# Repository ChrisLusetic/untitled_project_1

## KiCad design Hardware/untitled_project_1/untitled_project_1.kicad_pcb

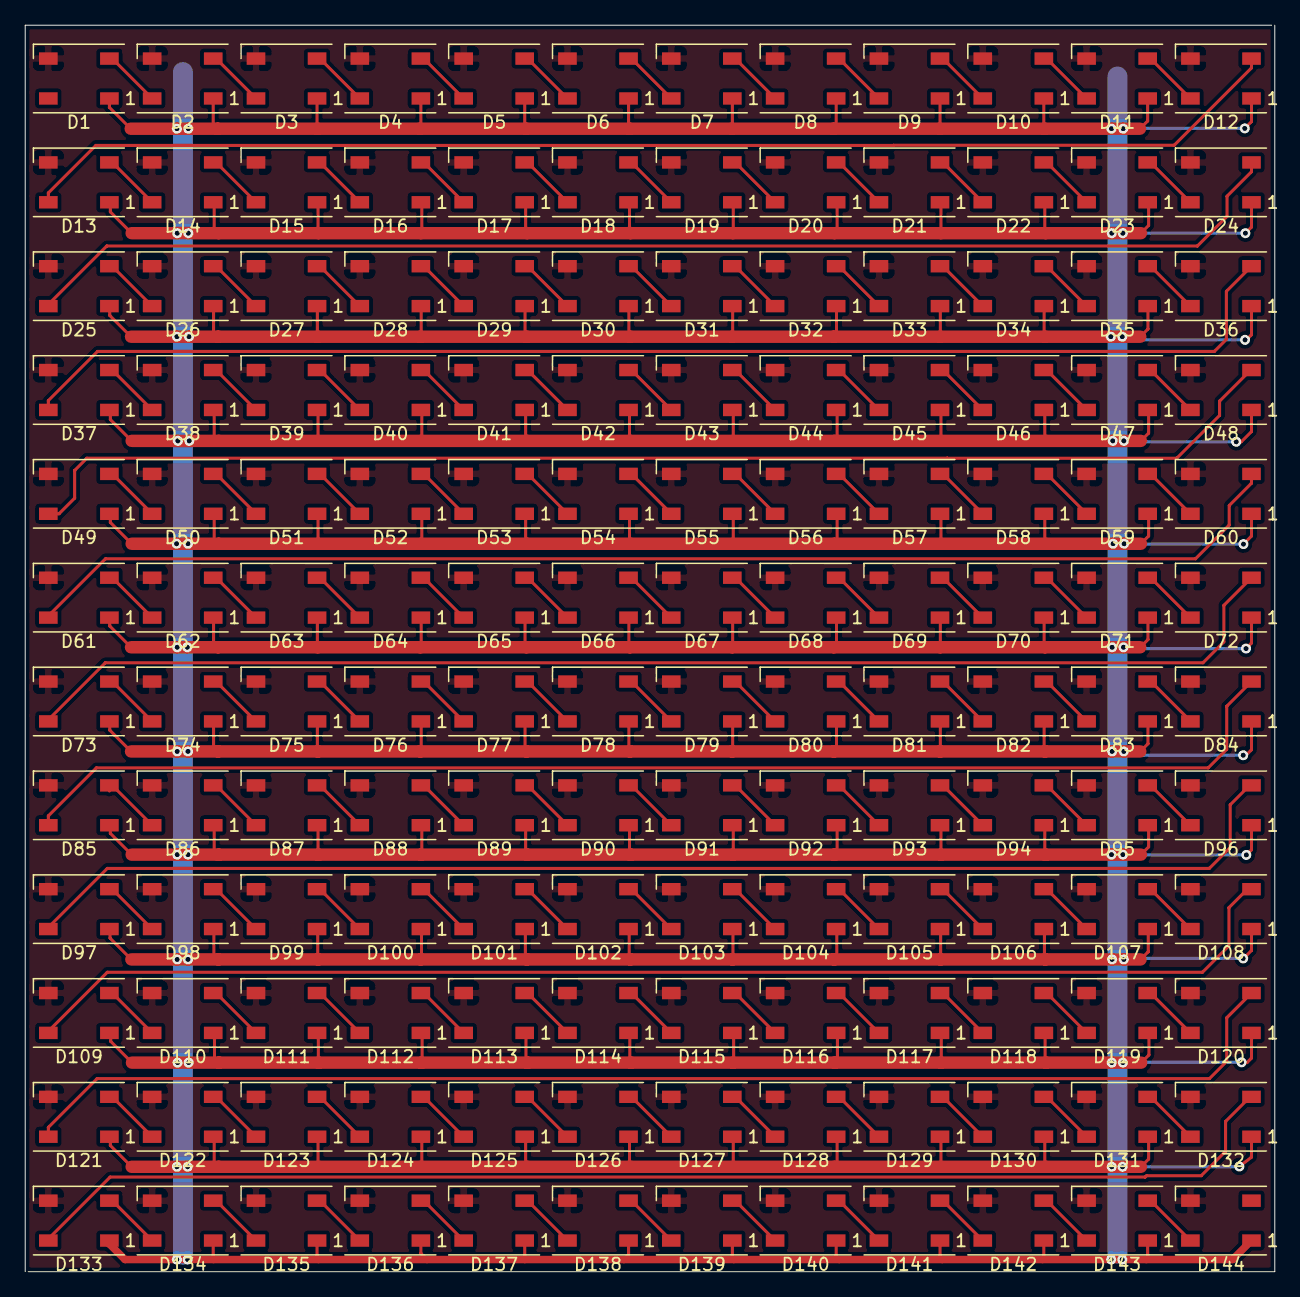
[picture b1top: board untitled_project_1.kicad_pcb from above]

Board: 2 copper layers, 100.2 x 100.0 mm, 144 parts (0 on the bottom side), 145 nets.

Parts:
D1, D2, D3, D4, D5, D6, D7, D8, D9, D10, D11, D12, D13, D14, D15, D16, D17, D18, D19, D20, D21, D22, D23, D24, D25, D26, D27, D28, D29, D30, D31, D32, D33, D34, D35, D36, D37, D38, D39, D40, D41, D42, D43, D44, D45, D46, D47, D48, D49, D50, D51, D52, D53, D54, D55, D56, D57, D58, D59, D60, D61, D62, D63, D64, D65, D66, D67, D68, D69, D70, D71, D72, D73, D74, D75, D76, D77, D78, D79, D80, D81, D82, D83, D84, D85, D86, D87, D88, D89, D90, D91, D92, D93, D94, D95, D96, D97, D98, D99, D100, D101, D102, D103, D104, D105, D106, D107, D108, D109, D110, D111, D112, D113, D114, D115, D116, D117, D118, D119, D120, D121, D122, D123, D124, D125, D126, D127, D128, D129, D130, D131, D132, D133, D134, D135, D136, D137, D138, D139, D140, D141, D142, D143, D144: WS2812B; LED_WS2812B_PLCC4_5.0x5.0mm_P3.2mm

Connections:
+5V: D1.1, D2.1, D3.1, D4.1, D5.1, D6.1, D7.1, D8.1, D9.1, D10.1, D11.1, D12.1, D13.1, D14.1, D15.1, D16.1, D17.1, D18.1, D19.1, D20.1, D21.1, D22.1, D23.1, D24.1, D25.1, D26.1, D27.1, D28.1, D29.1, D30.1, D31.1, D32.1, D33.1, D34.1, D35.1, D36.1, D37.1, D38.1, D39.1, D40.1, D41.1, D42.1, D43.1, D44.1, D45.1, D46.1, D47.1, D48.1, D49.1, D50.1, D51.1, D52.1, D53.1, D54.1, D55.1, D56.1, D57.1, D58.1, D59.1, D60.1, D61.1, D62.1, D63.1, D64.1, D65.1, D66.1, D67.1, D68.1, D69.1, D70.1, D71.1, D72.1, D73.1, D74.1, D75.1, D76.1, D77.1, D78.1, D79.1, D80.1, D81.1, D82.1, D83.1, D84.1, D85.1, D86.1, D87.1, D88.1, D89.1, D90.1, D91.1, D92.1, D93.1, D94.1, D95.1, D96.1, D97.1, D98.1, D99.1, D100.1, D101.1, D102.1, D103.1, D104.1, D105.1, D106.1, D107.1, D108.1, D109.1, D110.1, D111.1, D112.1, D113.1, D114.1, D115.1, D116.1, D117.1, D118.1, D119.1, D120.1, D121.1, D122.1, D123.1, D124.1, D125.1, D126.1, D127.1, D128.1, D129.1, D130.1, D131.1, D132.1, D133.1, D134.1, D135.1, D136.1, D137.1, D138.1, D139.1, D140.1, D141.1, D142.1, D143.1, D144.1
GND: D1.3, D2.3, D3.3, D4.3, D5.3, D6.3, D7.3, D8.3, D9.3, D10.3, D11.3, D12.3, D13.3, D14.3, D15.3, D16.3, D17.3, D18.3, D19.3, D20.3, D21.3, D22.3, D23.3, D24.3, D25.3, D26.3, D27.3, D28.3, D29.3, D30.3, D31.3, D32.3, D33.3, D34.3, D35.3, D36.3, D37.3, D38.3, D39.3, D40.3, D41.3, D42.3, D43.3, D44.3, D45.3, D46.3, D47.3, D48.3, D49.3, D50.3, D51.3, D52.3, D53.3, D54.3, D55.3, D56.3, D57.3, D58.3, D59.3, D60.3, D61.3, D62.3, D63.3, D64.3, D65.3, D66.3, D67.3, D68.3, D69.3, D70.3, D71.3, D72.3, D73.3, D74.3, D75.3, D76.3, D77.3, D78.3, D79.3, D80.3, D81.3, D82.3, D83.3, D84.3, D85.3, D86.3, D87.3, D88.3, D89.3, D90.3, D91.3, D92.3, D93.3, D94.3, D95.3, D96.3, D97.3, D98.3, D99.3, D100.3, D101.3, D102.3, D103.3, D104.3, D105.3, D106.3, D107.3, D108.3, D109.3, D110.3, D111.3, D112.3, D113.3, D114.3, D115.3, D116.3, D117.3, D118.3, D119.3, D120.3, D121.3, D122.3, D123.3, D124.3, D125.3, D126.3, D127.3, D128.3, D129.3, D130.3, D131.3, D132.3, D133.3, D134.3, D135.3, D136.3, D137.3, D138.3, D139.3, D140.3, D141.3, D142.3, D143.3, D144.3
unnamed: D1.2, D2.4
unnamed: D2.2, D3.4
unnamed: D3.2, D4.4
unnamed: D4.2, D5.4
unnamed: D5.2, D6.4
unnamed: D6.2, D7.4
unnamed: D7.2, D8.4
unnamed: D8.2, D9.4
unnamed: D10.2, D11.4
unnamed: D9.2, D10.4
unnamed: D11.2, D12.4
unnamed: D12.2, D13.4
unnamed: D13.2, D14.4
unnamed: D14.2, D15.4
unnamed: D15.2, D16.4
unnamed: D16.2, D17.4
unnamed: D17.2, D18.4
unnamed: D18.2, D19.4
unnamed: D19.2, D20.4
unnamed: D20.2, D21.4
unnamed: D21.2, D22.4
unnamed: D22.2, D23.4
unnamed: D23.2, D24.4
unnamed: D24.2, D25.4
unnamed: D25.2, D26.4
unnamed: D26.2, D27.4
unnamed: D27.2, D28.4
unnamed: D28.2, D29.4
unnamed: D29.2, D30.4
unnamed: D30.2, D31.4
unnamed: D31.2, D32.4
unnamed: D32.2, D33.4
unnamed: D33.2, D34.4
unnamed: D34.2, D35.4
unnamed: D35.2, D36.4
unnamed: D36.2, D37.4
unnamed: D37.2, D38.4
unnamed: D38.2, D39.4
unnamed: D39.2, D40.4
unnamed: D40.2, D41.4
unnamed: D41.2, D42.4
unnamed: D42.2, D43.4
unnamed: D43.2, D44.4
unnamed: D44.2, D45.4
unnamed: D45.2, D46.4
unnamed: D46.2, D47.4
unnamed: D47.2, D48.4
unnamed: D48.2, D49.4
unnamed: D49.2, D50.4
unnamed: D50.2, D51.4
unnamed: D51.2, D52.4
unnamed: D52.2, D53.4
unnamed: D53.2, D54.4
unnamed: D54.2, D55.4
unnamed: D55.2, D56.4
unnamed: D56.2, D57.4
unnamed: D57.2, D58.4
unnamed: D58.2, D59.4
unnamed: D59.2, D60.4
unnamed: D60.2, D61.4
unnamed: D61.2, D62.4
unnamed: D62.2, D63.4
unnamed: D63.2, D64.4
unnamed: D64.2, D65.4
unnamed: D65.2, D66.4
unnamed: D66.2, D67.4
unnamed: D67.2, D68.4
unnamed: D68.2, D69.4
unnamed: D69.2, D70.4
unnamed: D70.2, D71.4
unnamed: D71.2, D72.4
unnamed: D72.2, D73.4
unnamed: D73.2, D74.4
unnamed: D74.2, D75.4
unnamed: D75.2, D76.4
unnamed: D76.2, D77.4
unnamed: D77.2, D78.4
unnamed: D78.2, D79.4
unnamed: D79.2, D80.4
unnamed: D80.2, D81.4
unnamed: D81.2, D82.4
unnamed: D82.2, D83.4
unnamed: D83.2, D84.4
unnamed: D84.2, D85.4
unnamed: D85.2, D86.4
unnamed: D86.2, D87.4
unnamed: D87.2, D88.4
unnamed: D88.2, D89.4
unnamed: D89.2, D90.4
unnamed: D90.2, D91.4
unnamed: D91.2, D92.4
unnamed: D92.2, D93.4
unnamed: D93.2, D94.4
unnamed: D94.2, D95.4
unnamed: D95.2, D96.4
unnamed: D96.2, D97.4
unnamed: D97.2, D98.4
unnamed: D98.2, D99.4
unnamed: D100.2, D101.4
unnamed: D99.2, D100.4
unnamed: D101.2, D102.4
unnamed: D102.2, D103.4
unnamed: D103.2, D104.4
unnamed: D104.2, D105.4
unnamed: D105.2, D106.4
unnamed: D106.2, D107.4
unnamed: D107.2, D108.4
unnamed: D108.2, D109.4
unnamed: D109.2, D110.4
unnamed: D110.2, D111.4
unnamed: D111.2, D112.4
unnamed: D112.2, D113.4
unnamed: D113.2, D114.4
unnamed: D114.2, D115.4
unnamed: D115.2, D116.4
unnamed: D116.2, D117.4
unnamed: D117.2, D118.4
unnamed: D118.2, D119.4
unnamed: D119.2, D120.4
unnamed: D120.2, D121.4
unnamed: D121.2, D122.4
unnamed: D122.2, D123.4
unnamed: D123.2, D124.4
unnamed: D124.2, D125.4
unnamed: D125.2, D126.4
unnamed: D126.2, D127.4
unnamed: D127.2, D128.4
unnamed: D128.2, D129.4
unnamed: D129.2, D130.4
unnamed: D130.2, D131.4
unnamed: D131.2, D132.4
unnamed: D132.2, D133.4
unnamed: D133.2, D134.4
unnamed: D134.2, D135.4
unnamed: D135.2, D136.4
unnamed: D136.2, D137.4
unnamed: D137.2, D138.4
unnamed: D138.2, D139.4
unnamed: D139.2, D140.4
unnamed: D140.2, D141.4
unnamed: D141.2, D142.4
unnamed: D142.2, D143.4
unnamed: D143.2, D144.4

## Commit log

2020-06-22 added kicad project files
2020-06-22 routed 144led in array
2020-06-28 updated gitignore
2020-06-28 add power and programming schematics
2020-06-28 add footprints to szymbols:
